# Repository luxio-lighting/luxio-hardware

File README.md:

# Luxio hardware

## LX0001 · v1.0.0

A compact ESP32-S3 controller for addressable LED strips, with two 5 V logic
outputs, Wi-Fi, native USB and automatic wired-input priority.

### 3D views

**Top — isometric, USB bottom left / outputs top right**

**Underside — same view, flipped 180° around the long axis**

[Input-end view](LX0001/v1.0.0/Export/preview-centered-input-end.png) ·
[Top assembly drawing](LX0001/v1.0.0/Export/assembly-top.png) ·
[Bottom assembly drawing](LX0001/v1.0.0/Export/assembly-bottom.png)

### Hardware

| Item | Specification |
| --- | --- |
| Board | 60 × 20 mm, 4 layers, 1.6 mm FR-4 |
| Appearance | Black solder mask, white silkscreen, ENIG |
| MCU | ESP32-S3, external 4 MB flash, no PSRAM |
| Wireless | 2.4 GHz Wi-Fi with ceramic antenna |
| Wired input | 5–24 V DC; designed for a 5 A continuous strip load, pending thermal validation |
| USB | USB-C, native USB 2.0 data and 5 V power; no USB PD |
| LED signals | GPIO16 and GPIO17 translated from 3.3 V to 5 V |
| Button | Centered BOOT / GPIO18 user button |
| Wire connectors | HDGC 2060-452-HDGC, JLCPCB C55251566 |
| USB connector | GCT USB4215-03-A, JLCPCB C37616412 |
| Mounting | Two 2.2 mm holes for M2 screws |
| Fabrication | 0.30 mm minimum via drill; assembly on both sides |

USB-C and the two-wire input sit side by side on top at the same end. The two
output terminals sit at the opposite end. Viewed from above with input on the
left, input order is **GND, VCC** and output order is **GND, GPIO16, GPIO17, VCC**
from top to bottom. GPIO17 can be a second data channel or a clock signal,
depending on firmware and strip type.

### Power behavior

- A powered two-wire input supplies both controller and strip and takes
  priority over USB. USB remains available for data.
- USB alone automatically powers both the controller and LED output at 5 V.
- A 12 V or 24 V strip requires a matching wired supply. The board cannot
  automatically identify a strip's rated voltage and does not convert the
  output supply to a different strip voltage.
- USB has no onboard current limiter or power negotiation. Use a regulated
  5 V adapter and cable rated for the controller plus strip load. The USB
  connector design ceiling is 3 A total, pending thermal validation; it is
  not a current clamp. Use the wired input for the 5 A strip design target.
- Both 5 V data buffers are always enabled. Hardware pull-downs hold their
  inputs low during reset. GPIO5, GPIO6 and GPIO21 are unused.
- Power selection and data-buffer enables require no firmware changes.
  Firmware still generates the LED data on GPIO16/17.

Firmware is not included. See the [firmware interface](LX0001/v1.0.0/Source/firmware-interface.txt)
for pin assignments and boot recovery. A computer USB port can be used for
data with wired power present. USB-only strip loading does not enforce host
enumeration or suspend current budgets.
Hold the button during reset or power-up to enter ROM download mode; pressing
it alone does not reset a running controller.

### Enclosure

The button center is **(30, 10) mm**. Mounting-hole centers are **(9.5, 8) mm**
and **(42, 3) mm**, measured from the top-left board corner. Use screw heads
or standoffs no larger than 4.4 mm in diameter. Keep metal away from the
antenna and provide cable strain relief.

The USB mouth projects 0.50 mm beyond the input edge; the wire-entry face is
0.75 mm inside that edge. Account for the 1.25 mm difference when designing
case openings. Exact coordinates and antenna clearance are in
[mechanical.json](LX0001/v1.0.0/Source/mechanical.json).

Connector STEP models are from the **JLCEDA/EasyEDA Official Library**
([JLCEDA](https://lceda.cn/), [EasyEDA](https://easyeda.com/)). The HDGC model
is linked to the exact part. C37616412 links to a shared USB model named
`USB-C-SMD_GT-USB-7010B`; its body and shell-stake geometry match the selected
GCT drawing, but it is not a manufacturer-authenticated GCT model. Other
custom part models may be simplified. Use drawings and first articles to
verify enclosure fit. [Model provenance and alignment](LX0001/v1.0.0/Source/connector-model-update.json).

### Manufacturing and status

[Download the JLCPCB release package](LX0001/v1.0.0/Export/LX0001-v1.0.0-JLCPCB.zip).
Upload the Gerber ZIP, BOM and CPL together, using the included
[order settings](LX0001/v1.0.0/Export/JLCPCB-order-settings.txt). The current
release contains 83 fitted components; L104 is DNP. The component-only estimate
is $12.83 per board for 100 boards, excluding PCB and assembly costs.

The saved design passes ERC, DRC, schematic/PCB parity and the independent
drill-to-paste check, with zero open connections or mechanical DRC exceptions.
All routing vias have 0.30 mm drills. Copper-loss estimates include all
four layers; they are not thermal qualification.

**Status: fabrication data checked; hardware not yet production-qualified.**
Build and validate first articles before the planned 100-board lot. Electrical,
5 A thermal, RF, USB and assembly acceptance steps are recorded in
[first-article validation](LX0001/v1.0.0/Source/first-article-validation.txt).
No fabrication order has been placed.

### Files

- [Source](LX0001/v1.0.0/Source/): editable KiCad project, schematic, PCB,
  local footprints/models, electrical notes and verification/export tools.
- [Assets](LX0001/v1.0.0/Assets/): datasheets, supplier models and review evidence.
- [Export](LX0001/v1.0.0/Export/): current Gerbers, BOM/CPL, schematic PDF,
  assembly drawings, renders and validation records.

Open [LX0001.kicad_pro](LX0001/v1.0.0/Source/LX0001.kicad_pro) with KiCad 10.
The saved PCB is the final routed design; development placement/router scripts
are not a one-command rebuild recipe. See [tool notes](LX0001/v1.0.0/Source/tools/README.txt).
Historical files under `Assets/review-history` are not manufacturing inputs.

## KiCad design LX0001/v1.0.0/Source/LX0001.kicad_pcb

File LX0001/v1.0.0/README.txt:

LX0001 v1.0.0 — Luxio digital LED-strip controller

CURRENT STATUS: Four-layer fabrication data checked; first article not yet built.
Zero unrouted connections, zero schematic parity issues and zero ERC findings.
Four documented mechanical flags concern the recessed USB shell stakes.

Open Source/LX0001.kicad_pro in KiCad 10. The schematic and PCB are editable;
their symbol and footprint libraries are included in Source/libraries.
Custom connector/antenna 3D bodies are approximate preview models. Use the
manufacturer drawings, not the simplified bodies, for enclosure tolerances.

Design
60 x 20 mm, four copper layers, 1.6 mm FR-4, black mask and white silkscreen.
Bare ESP32-S3, 4 MB external flash, no PSRAM, ceramic 2.4 GHz edge antenna.
Two AHCT buffers translate GPIO16 and GPIO17 to 5 V data outputs.
The input terminal and underside USB-C share the end's y=10 mm centerline.
The two output terminals are centered as a pair at the opposite end.
The BOOT/GPIO18 button is centered at (30,10) mm. Two 2.2 mm M2 holes provide
case mounting; their centers are (9,17) and (42,3) mm from the top-left corner.

Connections, viewed from the top with the input at the left
Input, from antenna-side edge toward the opposite edge: GND, 5-24 V.
Output in the same direction: GND, GPIO16/5 V logic, GPIO17/5 V logic, VCC.
VCC follows the selected supply. It is not converted to the strip's voltage.
The design target is 5 A continuous from the wired supply, including 24 V/120 W.
An 8 A fuse provides fault protection; it is not a precise 5 A current limiter.

A powered wired input takes hardware priority over USB and enables strip power.
USB data stays connected. USB-only operation provides 5 V and has a shared
controller/strip current limit: approximately 0.44 A or 1.28 A, selected by
firmware only when the source permits it. USB strip power defaults OFF.
Firmware must enable it for a configured 5 V strip and enforce the remaining
current budget. A 12/24 V strip requires a suitable wired supply. The circuit
cannot identify a strip's rated voltage from its wires. No firmware is supplied.
See Source/firmware-interface.txt for the complete GPIO and startup contract.

Files
Source: native KiCad project, local libraries, connection table, design notes,
firmware interface and reproducible authoring/checking tools.
Assets: manufacturer datasheets, mechanical drawings, sourcing evidence and
the documented local routing-tool patch.
Export: schematic PDF, JLCPCB BOM/CPL, Gerber/drill archive, assembly drawings,
3D previews and verification reports. Manufacturing files are generated only
after the release checks in Source/tools/export_manufacturing.py pass.

Fabrication/assembly intent
Two-sided assembly, 1 oz outer / 0.5 oz inner copper, ENIG, 1.6 mm and black mask.
Order JLC04161H-7628 stackup; preserve the documented RF geometry.
Use JLCPCB standard two-side PCBA with assembler-designed panel rails/fiducials.
The GCT USB shell stakes are recessed inside the board. Four courtyard flags
refer to their annuli near the opposite-side terminal; top annuli are masked.
Prevent top-side solder protrusions and inspect this overlap on first articles.
See Source/fabrication-intent.txt and the exact connector drawing/notes.
Review the live JLCPCB placement preview and rotations before submitting an
order. No board order has been placed by this task.

Engineering status
The board has not been built or measured. CAD verification does not qualify
5 A thermal performance, antenna matching, USB behavior or assembly yield.
Build and test first articles using Source/first-article-validation.txt before
releasing the 100-board lot. Export/verification.json records the final CAD
checks when available; Source/current_path_review.txt separates copper modeling
from measured thermal performance. Initial RF matching requires measurement.

Cost snapshot, 2026-11-11
109 purchased placements, 52 unique purchased parts, one DNP tuning position
and 11 bare test pads. Components total approximately USD13.3690 per board or
USD1,336.90 per100, excluding PCB, assembly, setup, attrition, tax and shipping.
The dated component-price/stock evidence is not a reservation or a JLCPCB quote.

Editing/rebuilding
Native KiCad files are the primary editable deliverables. Running generate.py
without --board rebuilds only schematic/connection data. Running it with
--board REPLACES the PCB with initial placement and removes completed routing.
Do not run it on a manually revised routed board without preserving that work.

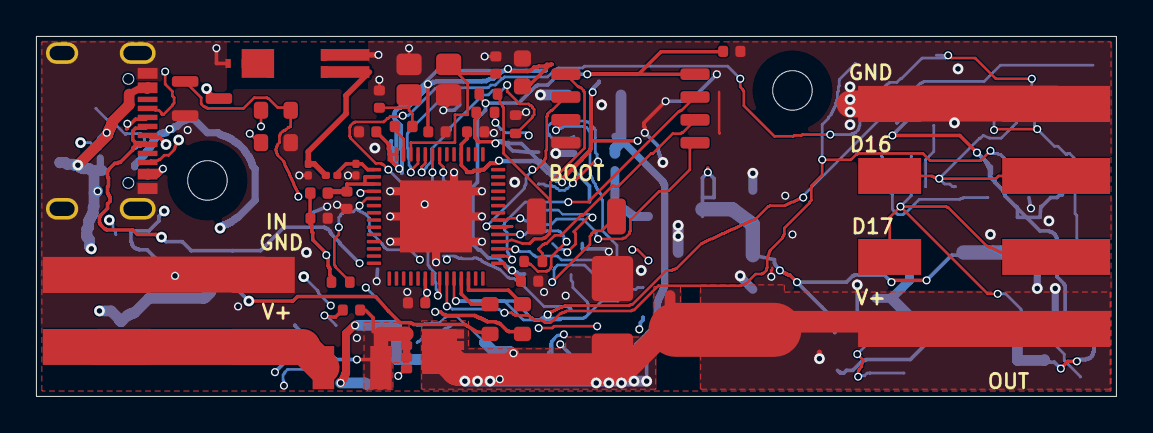
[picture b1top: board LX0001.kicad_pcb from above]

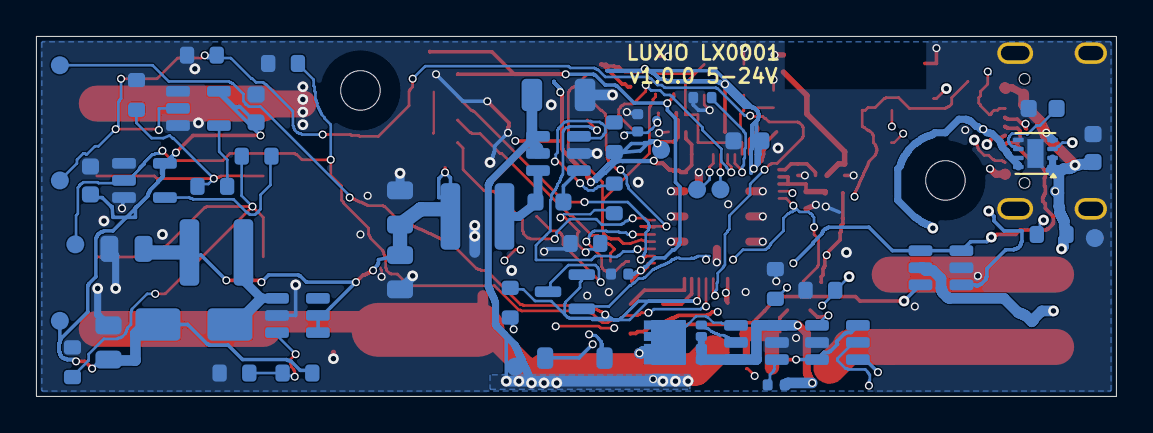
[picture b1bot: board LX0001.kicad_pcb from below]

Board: 4 copper layers, 60.0 x 20.0 mm, 96 parts (54 on the bottom side), 57 nets.

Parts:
ANT1: RFECA3216060A1T; Walsin_RFECA3216060A1T_Type1
C5, C7: 100nF 50V; C_0402_1005Metric
C6: 1uF 50V; C_0603_1608Metric
C8: 10uF 50V; C_1206_3216Metric
C9, C14, C17: 100nF 50V; C_0603_1608Metric
C10, C11, C12, C13: 22uF 25V; C_0805_2012Metric
C18: 1nF 50V; C_0603_1608Metric
C100, C107: 10uF 10V; C_0603_1608Metric
C101, C102, C103, C104, C105, C108, C110: 100nF 16V; C_0402_1005Metric
C106, C109, C111: 1uF 25V; C_0402_1005Metric
C112, C113: 18pF 50V C0G; C_0402_1005Metric
C114, C115: 1.5pF 50V C0G; C_0201_0603Metric
D1: 1N4148W; D_SOD-123
D2: SS14; D_SMA
D3: SMBJ24A; D_SMB
D4: BAT54C; SOT-23
F1: 8A 32V; Fuse_SART_S1206_FA
H1, H2: MountingHole_2.2mm_M2
J1: USB-TYPE-C-018; USB_C_DEALON_USB_TYPE_C_018
J2, J3, J4: 2060-452-HDGC; HDGC_2060_452
L1: 10uH 1.5A Isat1.95A; L_Sunlord_SWPA4030S
L2: 4.7uH 2A Isat2.9A; L_Sunlord_SWPA4030S
L100: 2nH 900mA; L_0402_1005Metric
L101: 24nH; L_0402_1005Metric
L102: 2.7nH; L_0201_0603Metric
L104: DNP 0R antenna tune; Walsin_RFECA_Tuner_0402
Q1, Q3: CSD18543Q3A; VSON-8_3.3x3.3mm_P0.65mm_NexFET
Q2: MMBT3904; SOT-23
R1, R2: 5.1k; R_0603_1608Metric
R3, R4: 22; R_0603_1608Metric
R10, R13, R17, R18, R22, R28, R29: 100k; R_0603_1608Metric
R12: 47k; R_0603_1608Metric
R14: 73.2k; R_0603_1608Metric
R15, R24, R30: 10k; R_0603_1608Metric
R16, R27: 100; R_0603_1608Metric
R23: 22k; R_0603_1608Metric
R100, R101, R102, R103, R110: 10k; R_0402_1005Metric
R105: 0; R_0402_1005Metric
SW1: TS-1088-AR02016; SW_TS-1088-AR02016
TP1: GND; TestPoint_Pad_D1.0mm
TP2: +3V3; TestPoint_Pad_D1.0mm
TP3: ESP_EN; TestPoint_Pad_D0.5mm
TP6: GPIO16; TestPoint_Pad_D1.0mm
TP7: GPIO17; TestPoint_Pad_D1.0mm
TP8: +5V_DATA; TestPoint_Pad_D1.0mm
TP9: VSYS; TestPoint_Pad_D1.0mm
TP10: GPIO18_BUTTON; TestPoint_Pad_D1.0mm
TP11: UART_TX; TestPoint_Pad_D1.0mm
TP12: UART_RX; TestPoint_Pad_D1.0mm
U1: ESP32-S3; QFN-56-1EP_7x7mm_P0.4mm_EP4x4mm
U2: USBLC6-2SC6; SOT-23-6
U3, U5: LM74700QDBVRQ1; SOT-23-6
U4: TPS22965DSGR; Texas_DSG0008A_WSON-8-1EP_2x2mm_P0.5mm_EP0.9x1.6mm
U6: LMR51410YFDBVR; SOT-23-6
U7: MT3608; SOT-23-6
U8, U9: SN74AHCT1G125DBVR; SOT-23-5
U10: W25Q32JVSSIQ; SOIC-8_5.3x5.3mm_P1.27mm
Y1: 40MHz 12pF 10ppm; Crystal_SMD_3225-4Pin_3.2x2.5mm

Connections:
+3V3: C10.1, C11.1, C12.1, C100.1, C101.1, C103.1, C104.1, C105.1, C106.1, C107.1, L1.2, L2.1, L100.1, R22.1, R30.1, R100.1, R101.1, TP2.1, U1.20, U1.46, U1.55, U1.56, U7.4, U7.5
+5V_DATA: C13.1, C14.1, C17.1, D2.1, R14.1, TP8.1, U8.5, U9.5
ANT_TUNE: ANT1.2, L104.1
BOOST_FB: R14.2, R15.1, U7.3
BOOST_SW: D2.2, L2.2, U7.1
BOOT: D4.1, R101.2, U1.5
BUCK_BST: C9.1, U6.1
BUCK_FB: R22.2, R23.1, U6.3
BUCK_FB_LOW: R23.2, R24.1
BUCK_SW: C9.2, L1.1, U6.6
BUTTON_COMMON: D4.3, SW1.1
CC1: J1.A5, R1.1
CC2: J1.B5, R2.1
DATA16_5V: R16.1, U8.4
DATA16_OUT: J3.1, R16.2, R17.1
DATA17_5V: R27.1, U9.4
DATA17_OUT: J4.2, R27.2, R28.1
DC_FUSED: C5.2, D1.2, F1.2, Q1.1, Q1.2, Q1.3, U3.3, U3.6
DC_GATE: Q1.4, U3.5
DC_IN: F1.1, J2.2
DC_SENSE_B: Q2.1, R12.2, R13.1
DC_SENSE_R: D1.1, R12.1
DC_VCAP: C5.1, U3.1
ESP_EN: C111.1, R100.2, TP3.1, U1.4
FLASH_CLK: R105.2, U10.6
FLASH_CS: R110.2, U1.32, U10.1
FLASH_IO0: U1.35, U10.5
FLASH_IO1: U1.34, U10.2
FLASH_IO2: U1.31, U10.3
FLASH_IO3: U1.30, U10.7
GND: ANT1.3, C6.2, C8.2, C10.2, C11.2, C12.2, C13.2, C14.2, C17.2, C18.2, C100.2, C101.2, C102.2, C103.2, C104.2, C105.2, C106.2, C107.2, C108.2, C109.2, C110.2, C111.2, C112.2, C113.2, C114.2, C115.2, D3.2, J1.A1, J1.A12, J1.B1, J1.B12, J1.SH, J2.1, J3.2, L104.2, Q2.2, R1.2, R2.2, R13.2, R15.2, R17.2, R18.2, R24.2, R28.2, R29.2, R102.2, R103.2, SW1.2, TP1.1, U1.57, U2.2, U3.2, U4.5, U4.9, U5.2, U6.2, U7.2, U8.1, U8.3, U9.1, U9.3, U10.4, Y1.2, Y1.4
GPIO16: R18.1, TP6.1, U1.22, U8.2
GPIO17: R29.1, TP7.1, U1.23, U9.2
GPIO18_BUTTON: D4.2, R30.2, TP10.1, U1.24
RF_50: ANT1.1, C115.1, L102.2
RF_CHIP: C114.1, L102.1, U1.1
SPICLK: R105.1, U1.33
STRAP45: R102.1, U1.51
STRAP46: R103.1, U1.52
UART_RX: TP12.1, U1.50
UART_TX: TP11.1, U1.49
USB_5V: C6.1, J1.A4, J1.A9, J1.B4, J1.B9, R10.1, U2.5, U4.1, U4.2, U4.4
USB_DM: R3.2, U1.25
USB_DM_CONN: J1.A7, J1.B7, R3.1, U2.1, U2.6
USB_DP: R4.2, U1.26
USB_DP_CONN: J1.A6, J1.B6, R4.1, U2.3, U2.4
USB_ENABLE: Q2.3, R10.2, U4.3
USB_GATE: Q3.4, U5.5
USB_SLEW: C18.1, U4.6
USB_SWITCHED: C7.2, Q3.1, Q3.2, Q3.3, U4.7, U4.8, U5.3, U5.6
USB_VCAP: C7.1, U5.1
VDD3P3_RF: C102.1, L100.2, U1.2, U1.3
VDD_SPI: C108.1, C109.1, C110.1, R110.1, U1.29, U10.8
VSYS: C8.1, D3.1, J4.1, Q1.5, Q3.5, TP9.1, U3.4, U5.4, U6.4, U6.5
XTAL_N: C113.1, U1.53, Y1.3
XTAL_P: L101.1, U1.54
XTAL_P_CRYSTAL: C112.1, L101.2, Y1.1

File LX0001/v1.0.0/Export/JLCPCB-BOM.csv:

Comment,Designator,Footprint,LCSC Part #,Quantity
TPS22965DSGR,U4,Package_SON:Texas_DSG0008A_WSON-8-1EP_2x2mm_P0.5mm_EP0.9x1.6mm,C122837,1
RFECA3216060A1T,ANT1,Core:Walsin_RFECA3216060A1T_Type1,C127620,1
10uF 50V,C8,Capacitor_SMD:C_1206_3216Metric,C13585,1
100nF 50V,"C14,C17,C9",Capacitor_SMD:C_0603_1608Metric,C14663,3
73.2k,R14,Resistor_SMD:R_0603_1608Metric,C14890,1
100nF 16V,"C101,C102,C103,C104,C105,C108,C110",Capacitor_SMD:C_0402_1005Metric,C1525,7
18pF 50V C0G,"C112,C113",Capacitor_SMD:C_0402_1005Metric,C1549,2
1uF 50V,C6,Capacitor_SMD:C_0603_1608Metric,C15849,1
1nF 50V,C18,Capacitor_SMD:C_0603_1608Metric,C1588,1
1.5pF 50V C0G,"C114,C115",Capacitor_SMD:C_0201_0603Metric,C161414,2
0,R105,Resistor_SMD:R_0402_1005Metric,C17168,1
W25Q32JVSSIQ,U10,Package_SO:SOIC-8_5.3x5.3mm_P1.27mm,C179173,1
2nH 900mA,L100,Inductor_SMD:L_0402_1005Metric,C18216,1
8A 32V,F1,LX0001:Fuse_SART_S1206_FA,C183158,1
10uF 10V,"C100,C107",Capacitor_SMD:C_0603_1608Metric,C19702,2
MMBT3904,Q2,Package_TO_SOT_SMD:SOT-23,C20526,1
BAT54C,D4,Package_TO_SOT_SMD:SOT-23,C2135,1
100,"R16,R27",Resistor_SMD:R_0603_1608Metric,C22775,2
5.1k,"R1,R2",Resistor_SMD:R_0603_1608Metric,C23186,2
22,"R3,R4",Resistor_SMD:R_0603_1608Metric,C23345,2
SS14,D2,Diode_SMD:D_SMA,C2480,1
10k,"R100,R101,R102,R103,R110",Resistor_SMD:R_0402_1005Metric,C25744,5
100k,"R10,R13,R17,R18,R22,R28,R29",Resistor_SMD:R_0603_1608Metric,C25803,7
10k,"R15,R24,R30",Resistor_SMD:R_0603_1608Metric,C25804,3
47k,R12,Resistor_SMD:R_0603_1608Metric,C25819,1
ESP32-S3,U1,Package_DFN_QFN:QFN-56-1EP_7x7mm_P0.4mm_EP4x4mm,C2913192,1
USB-TYPE-C-018,J1,LX0001:USB_C_DEALON_USB_TYPE_C_018,C2927038,1
LM74700QDBVRQ1,"U3,U5",Package_TO_SOT_SMD:SOT-23-6,C2941042,2
100nF 50V,"C5,C7",Capacitor_SMD:C_0402_1005Metric,C307331,2
22k,R23,Resistor_SMD:R_0603_1608Metric,C31850,1
LMR51410YFDBVR,U6,Package_TO_SOT_SMD:SOT-23-6,C32347484,1
10uH 1.5A Isat1.95A,L1,Inductor_SMD:L_Sunlord_SWPA4030S,C38117,1
22uF 25V,"C10,C11,C12,C13",Capacitor_SMD:C_0805_2012Metric,C45783,4
1uF 25V,"C106,C109,C111",Capacitor_SMD:C_0402_1005Metric,C52923,3
2060-452-HDGC,"J2,J3,J4",LX0001:HDGC_2060_452,C55251566,3
4.7uH 2A Isat2.9A,L2,Inductor_SMD:L_Sunlord_SWPA4030S,C57269,1
40MHz 12pF 10ppm,Y1,Crystal:Crystal_SMD_3225-4Pin_3.2x2.5mm,C655034,1
TS-1088-AR02016,SW1,LX0001:SW_TS-1088-AR02016,C720477,1
SMBJ24A,D3,Diode_SMD:D_SMB,C7470946,1
SN74AHCT1G125DBVR,"U8,U9",Package_TO_SOT_SMD:SOT-23-5,C7484,2
USBLC6-2SC6,U2,Package_TO_SOT_SMD:SOT-23-6,C7519,1
1N4148W,D1,Diode_SMD:D_SOD-123,C81598,1
CSD18543Q3A,"Q1,Q3",Package_SON:VSON-8_3.3x3.3mm_P0.65mm_NexFET,C840100,2
MT3608,U7,Package_TO_SOT_SMD:SOT-23-6,C84817,1
24nH,L101,Inductor_SMD:L_0402_1005Metric,C913699,1
2.7nH,L102,Inductor_SMD:L_0201_0603Metric,C98043,1

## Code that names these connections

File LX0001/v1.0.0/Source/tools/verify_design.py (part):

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      for a in pads:
       if a.GetNetname()!=net:errors.append(f'{ref}.{pin} PCB {a.GetNetname()}, expected {net}')
    byref={v['ref']:v for v in parts};u=byref['U1']['pins']
    for pin,net in {'5':'BOOT','22':'GPIO16','23':'GPIO17','24':'GPIO18_BUTTON','25':'USB_DM','26':'USB_DP','29':'VDD_SPI','57':'GND'}.items():
     if u.get(pin)!=net:errors.append('ESP32 physical pin mapping incorrect '+pin)
    assert byref['U10']['value']=='W25Q32JVSSIQ' and byref['U1']['value']=='ESP32-S3'
    assert byref['D4']['pins']=={'1':'BOOT','2':'GPIO18_BUTTON','3':'BUTTON_COMMON'}
    assert byref['J2']['pins']=={'1':'GND','2':'DC_IN'}
    assert byref['J3']['pins']=={'1':'DATA16_OUT','2':'GND'}
    assert byref['J4']['pins']=={'1':'VSYS','2':'DATA17_OUT'}
    assert all(pin not in u for pin in ['6','7','9','10','11','27'])
    assert byref['U4']['value']=='TPS22965DSGR'
    assert byref['U4']['pins']=={'1':'USB_5V','2':'USB_5V','3':'USB_ENABLE','4':'USB_5V','5':'GND','6':'USB_SLEW','7':'USB_SWITCHED','8':'USB_SWITCHED','9':'GND'}
    assert byref['U8']['pins']['1']=='GND' and byref['U9']['pins']['1']=='GND'
    assert not ({'Q4','Q5','Q6','Q7','Q8'} & set(byref))
    assert byref['R1']['pins']=={'1':'CC1','2':'GND'} and byref['R2']['pins']=={'1':'CC2','2':'GND'}
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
